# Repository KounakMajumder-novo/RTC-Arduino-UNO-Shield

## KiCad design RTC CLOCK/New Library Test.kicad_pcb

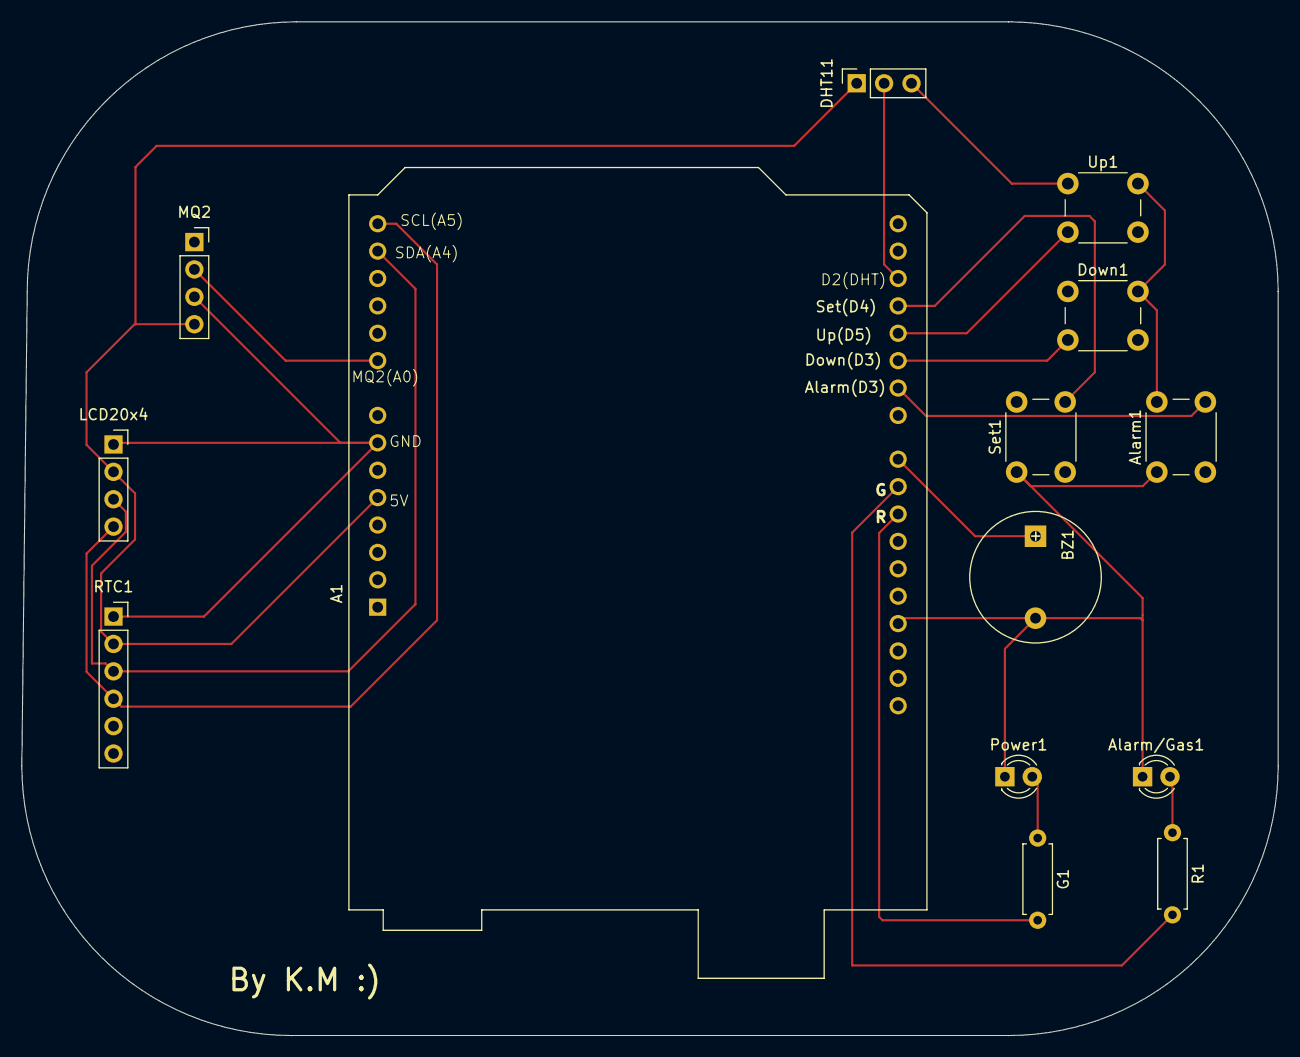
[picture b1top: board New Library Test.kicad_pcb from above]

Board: 2 copper layers, 116.5 x 94.0 mm, 14 parts (0 on the bottom side), 16 nets.

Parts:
A1: Arduino_UNO_R3
Alarm1: SW_Push; SW_PUSH_6mm
Alarm/Gas1: Red; LED_D3.0mm
BZ1: Buzzer; Buzzer_12x9.5RM7.6
DHT11: Conn_01x03_Socket; PinSocket_1x03_P2.54mm_Vertical
Down1: SW_Push; SW_PUSH_6mm
G1: 220; R_Axial_DIN0207_L6.3mm_D2.5mm_P7.62mm_Horizontal
LCD20x4: Conn_01x04_Socket; PinSocket_1x04_P2.54mm_Vertical
MQ2: Conn_01x04_Socket; PinSocket_1x04_P2.54mm_Vertical
Power1: Green; LED_D3.0mm
R1: 220; R_Axial_DIN0207_L6.3mm_D2.5mm_P7.62mm_Horizontal
RTC1: Conn_01x06_Socket; PinSocket_1x06_P2.54mm_Vertical
Set1: SW_Push; SW_PUSH_6mm
Up1: SW_Push; SW_PUSH_6mm

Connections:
5V: A1.5 (+5V), DHT11.1, LCD20x4.2, MQ2.4, RTC1.2
unnamed: A1.9 (A0), MQ2.2
unnamed: A1.17 (D2), DHT11.2
unnamed: A1.18 (D3), Set1.2
unnamed: A1.19 (D4), Up1.2
unnamed: A1.20 (D5), Down1.2
unnamed: A1.21 (D6), Alarm1.2
unnamed: A1.23 (D8), BZ1.1 (+)
unnamed: A1.24 (D9), R1.2
unnamed: A1.25 (D10), G1.2
unnamed: Alarm/Gas1.2 (A), R1.1
unnamed: A1.29 (GND), Alarm1.1, Alarm/Gas1.1 (K), BZ1.2 (-), DHT11.3, Down1.1, Power1.1 (K), Set1.1, Up1.1
unnamed: A1.7 (GND), LCD20x4.1, MQ2.3, RTC1.1
unnamed: A1.13 (SDA/A4), LCD20x4.3, RTC1.3
unnamed: A1.14 (SCL/A5), LCD20x4.4, RTC1.4
unnamed: G1.1, Power1.2 (A)

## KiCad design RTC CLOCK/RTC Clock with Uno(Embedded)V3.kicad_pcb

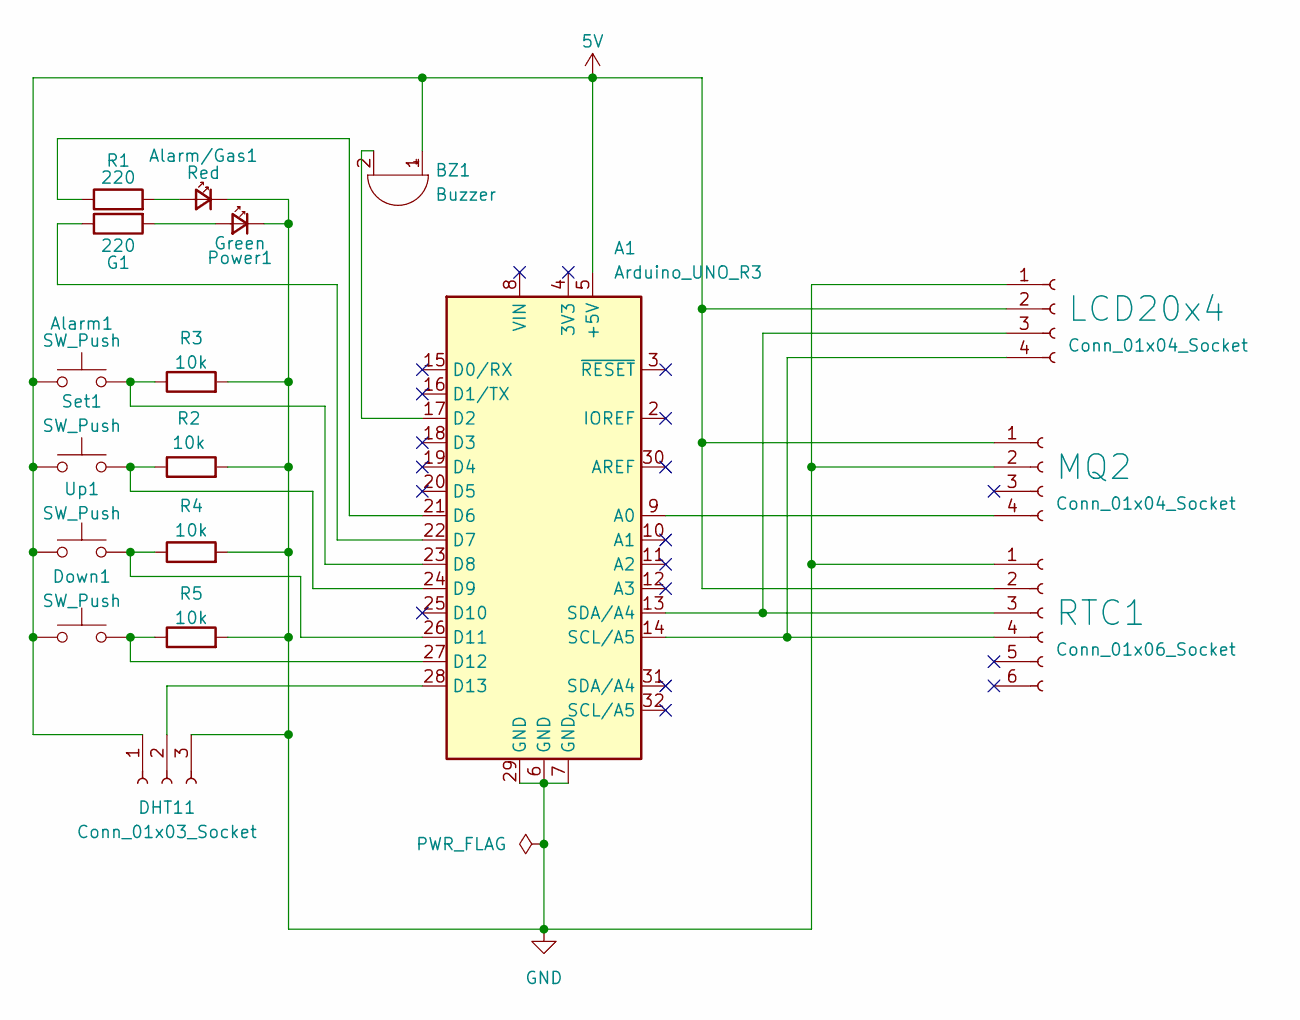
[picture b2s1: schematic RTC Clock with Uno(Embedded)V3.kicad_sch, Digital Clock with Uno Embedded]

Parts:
A1: Arduino_UNO_R3
Alarm1: SW_Push; SW_PUSH-12mm
Alarm/Gas1: Red; LED_D5.0mm
BZ1: Buzzer; Buzzer_12x9.5RM7.6
DHT11: Conn_01x03_Socket; PinSocket_1x03_P2.54mm_Vertical
Down1: SW_Push; SW_PUSH-12mm
G1: 220; R_Axial_DIN0207_L6.3mm_D2.5mm_P7.62mm_Horizontal
LCD20x4: Conn_01x04_Socket; PinSocket_1x04_P2.54mm_Vertical
MQ2: Conn_01x04_Socket; PinSocket_1x04_P2.54mm_Vertical
Power1: Green; LED_D5.0mm
R1: 220; R_Axial_DIN0207_L6.3mm_D2.5mm_P7.62mm_Horizontal
R2, R3, R4, R5: 10k; R_Axial_DIN0207_L6.3mm_D2.5mm_P10.16mm_Horizontal
RTC1: Conn_01x06_Socket; PinSocket_1x06_P2.54mm_Vertical
Set1: SW_Push; SW_PUSH-12mm
Up1: SW_Push; SW_PUSH-12mm

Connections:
5V: A1.5 (+5V), Alarm1.1, BZ1.1 (+), DHT11.1, Down1.1, LCD20x4.2, MQ2.1, RTC1.2, Set1.1, Up1.1
GND: A1.6 (GND), A1.7 (GND), A1.29 (GND), Alarm/Gas1.1 (K), DHT11.3, LCD20x4.1, MQ2.2, Power1.1 (K), R2.2, R3.2, R4.2, R5.2, RTC1.1
unnamed: A1.9 (A0), MQ2.4
unnamed: A1.17 (D2), BZ1.2 (-)
unnamed: A1.21 (D6), R1.1
unnamed: A1.22 (D7), G1.1
unnamed: A1.23 (D8), Alarm1.2, R3.1
unnamed: A1.24 (D9), R2.1, Set1.2
unnamed: A1.26 (D11), R4.1, Up1.2
unnamed: A1.27 (D12), Down1.2, R5.1
unnamed: A1.28 (D13), DHT11.2
unnamed: Alarm/Gas1.2 (A), R1.2
unnamed: A1.13 (SDA/A4), LCD20x4.3, RTC1.3
unnamed: A1.14 (SCL/A5), LCD20x4.4, RTC1.4
unnamed: G1.2, Power1.2 (A)

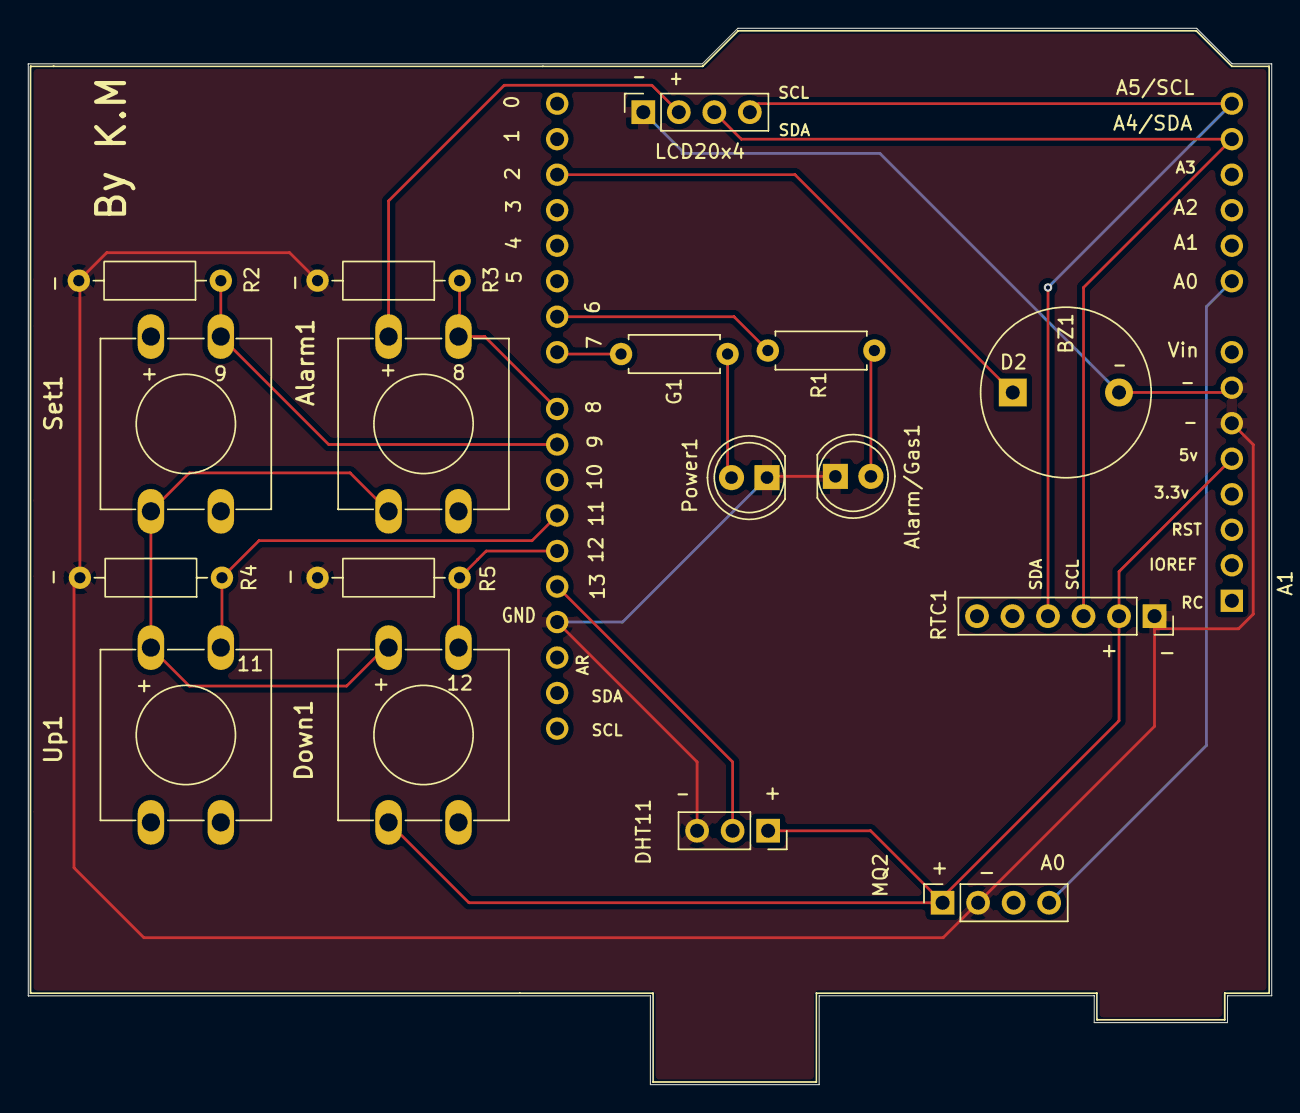
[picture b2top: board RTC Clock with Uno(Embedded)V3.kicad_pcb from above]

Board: 2 copper layers, 88.9 x 75.6 mm, 18 parts (0 on the bottom side), 15 nets.
